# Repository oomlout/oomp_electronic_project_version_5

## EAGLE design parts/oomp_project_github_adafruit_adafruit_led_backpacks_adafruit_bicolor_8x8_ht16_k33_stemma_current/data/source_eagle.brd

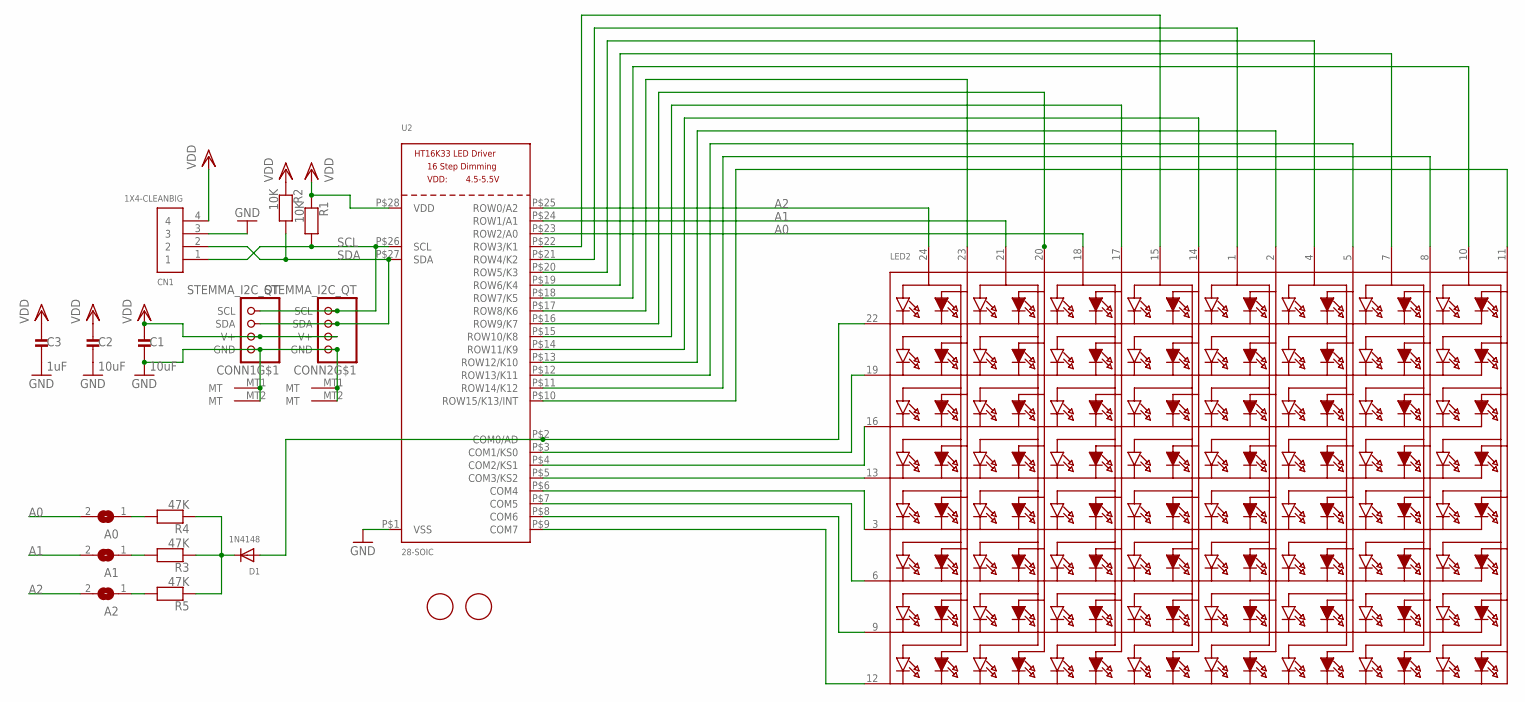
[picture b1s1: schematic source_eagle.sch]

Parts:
A0, A1, A2: SOLDERJUMPERREFLOW_NOPASTE; SOLDERJUMPER_REFLOW_NOPASTE
C1, C2: 10uF; 0805-NO
C3: 1uF; 0603-NO
CN1: 1X4-CLEANBIG; 1X04-CLEANBIG
CONN1, CONN2: STEMMA_I2C_QT; JST_SH4
D1: 1N4148; SOD-323
LED2: DISP_SEGMENT_8X8_BICOLOR_ROWCATHODEMI2A883XX; SEGMENT_BICOL_BL-M12A883XX
R1, R2: 10K; 0603-NO
R3, R4, R5: 47K; 0603-NO
U2: 28-SOIC; SOP28_300MIL
U$1, U$2: FIDUCIAL; FIDUCIAL_1MM

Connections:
A0: A0.2, LED2.18 (A5), U2.P$23 (ROW2/A0)
A1: A1.2, LED2.21 (A3), U2.P$24 (ROW1/A1)
A2: A2.2, LED2.24 (A1), U2.P$25 (ROW0/A2)
GND: C1.2, C2.2, C3.2, CN1.3, CONN1.1 (GND), CONN1.MT1 (MT), CONN1.MT2 (MT), CONN2.1 (GND), CONN2.MT1 (MT), CONN2.MT2 (MT), U2.P$1 (VSS)
unnamed: LED2.12 (K8), U2.P$9 (COM7)
unnamed: LED2.9 (K7), U2.P$8 (COM6)
unnamed: LED2.6 (K6), U2.P$7 (COM5)
unnamed: LED2.3 (K5), U2.P$6 (COM4)
unnamed: LED2.13 (K4), U2.P$5 (COM3/KS2)
unnamed: LED2.16 (K3), U2.P$4 (COM2/KS1)
unnamed: LED2.19 (K2), U2.P$3 (COM1/KS0)
unnamed: D1.A, LED2.22 (K1), U2.P$2 (COM0/AD)
unnamed: A2.1, R5.2
unnamed: LED2.8 (A14), U2.P$11 (ROW14/K12)
unnamed: LED2.5 (A12), U2.P$12 (ROW13/K11)
unnamed: LED2.11 (A16), U2.P$10 (ROW15/K13/INT)
unnamed: D1.C, R3.1, R4.1, R5.1
unnamed: A1.1, R3.2
unnamed: A0.1, R4.2
unnamed: LED2.10 (A15), U2.P$18 (ROW7/K5)
unnamed: LED2.7 (A13), U2.P$19 (ROW6/K4)
unnamed: LED2.1 (A9), U2.P$21 (ROW4/K2)
unnamed: LED2.15 (A7), U2.P$22 (ROW3/K1)
unnamed: LED2.4 (A11), U2.P$20 (ROW5/K3)
unnamed: LED2.23 (A2), U2.P$17 (ROW8/K6)
unnamed: LED2.20 (A4), U2.P$16 (ROW9/K7)
unnamed: LED2.14 (A8), U2.P$14 (ROW11/K9)
unnamed: LED2.17 (A6), U2.P$15 (ROW10/K8)
unnamed: LED2.2 (A10), U2.P$13 (ROW12/K10)
SCL: CN1.1, CONN1.4 (SCL), CONN2.4 (SCL), R1.2, U2.P$26 (SCL)
SDA: CN1.2, CONN1.3 (SDA), CONN2.3 (SDA), R2.2, U2.P$27 (SDA)
VDD: C1.1, C2.1, C3.1, CN1.4, CONN1.2 (V+), CONN2.2 (V+), R1.1, R2.1, U2.P$28 (VDD)

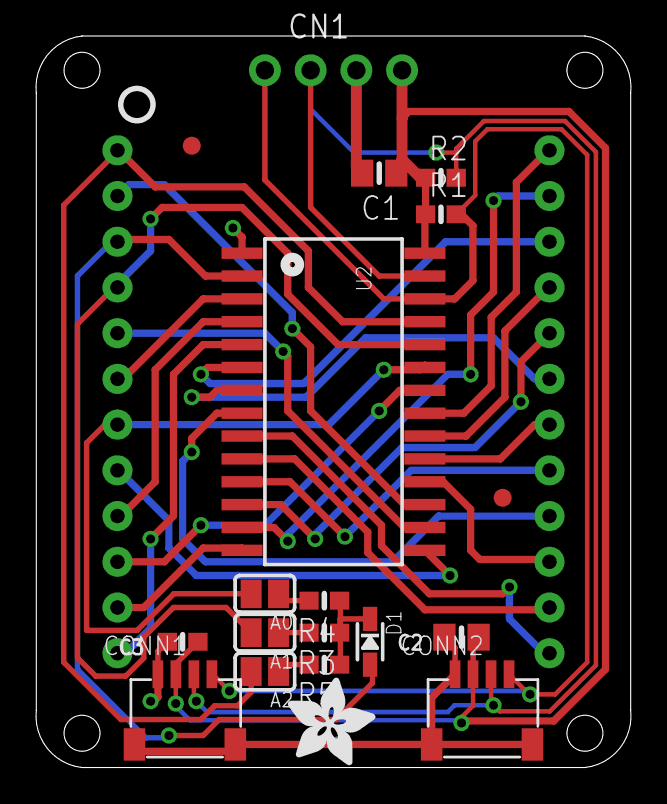
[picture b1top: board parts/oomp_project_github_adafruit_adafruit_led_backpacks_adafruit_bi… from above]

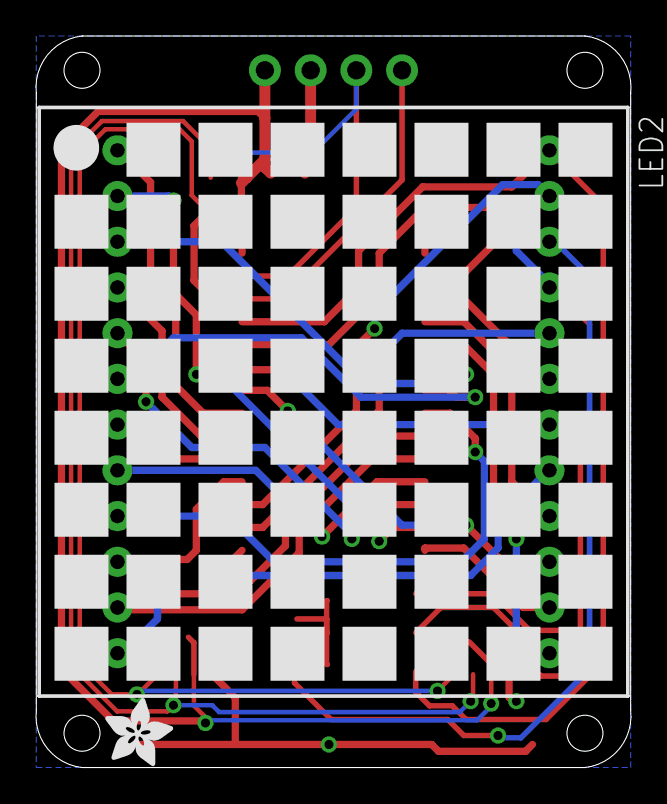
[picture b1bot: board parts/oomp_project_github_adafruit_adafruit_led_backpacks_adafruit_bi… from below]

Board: 2 copper layers, 33.1 x 40.6 mm, 37 parts (7 on the bottom side), 32 nets.

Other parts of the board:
E$2: ADAFRUIT_3.5MM
PLABEL0: PLABEL0
PLABEL1: PLABEL1
PLABEL2: PLABEL2
PLABEL3: PLABEL3
PLABEL4: PLABEL4
PLABEL5: PLABEL5
PLABEL6: PLABEL6
PLABEL7: PLABEL7
PLABEL8: PLABEL8
PLABEL9: PLABEL9
PLABEL10: PLABEL10
PLABEL11: PLABEL11
PLABEL12: PLABEL12
PLABEL13: PLABEL13
PLABEL14: PLABEL14
U$3: ADAFRUIT_5MM
U$4: PCBFEAT-REV-040

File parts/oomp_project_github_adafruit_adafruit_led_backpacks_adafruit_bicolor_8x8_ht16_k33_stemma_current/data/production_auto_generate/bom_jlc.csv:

Comment,Designator,Footprint,LCSC Part #
,E$2,Adafruit Bicolor 8x8 HT16K33 STEMMA-import-fps:ADAFRUIT_3.5MM,
,U$3,Adafruit Bicolor 8x8 HT16K33 STEMMA-import-fps:ADAFRUIT_5MM,
,U$4,Adafruit Bicolor 8x8 HT16K33 STEMMA-import-fps:PCBFEAT-REV-040,
,PLABEL0,Adafruit Bicolor 8x8 HT16K33 STEMMA-import-fps:PLABEL0,
,PLABEL1,Adafruit Bicolor 8x8 HT16K33 STEMMA-import-fps:PLABEL1,
,PLABEL10,Adafruit Bicolor 8x8 HT16K33 STEMMA-import-fps:PLABEL10,
,PLABEL11,Adafruit Bicolor 8x8 HT16K33 STEMMA-import-fps:PLABEL11,
,PLABEL12,Adafruit Bicolor 8x8 HT16K33 STEMMA-import-fps:PLABEL12,
,PLABEL13,Adafruit Bicolor 8x8 HT16K33 STEMMA-import-fps:PLABEL13,
,PLABEL14,Adafruit Bicolor 8x8 HT16K33 STEMMA-import-fps:PLABEL14,
,PLABEL2,Adafruit Bicolor 8x8 HT16K33 STEMMA-import-fps:PLABEL2,
,PLABEL3,Adafruit Bicolor 8x8 HT16K33 STEMMA-import-fps:PLABEL3,
,PLABEL4,Adafruit Bicolor 8x8 HT16K33 STEMMA-import-fps:PLABEL4,
,PLABEL5,Adafruit Bicolor 8x8 HT16K33 STEMMA-import-fps:PLABEL5,
,PLABEL6,Adafruit Bicolor 8x8 HT16K33 STEMMA-import-fps:PLABEL6,
,PLABEL7,Adafruit Bicolor 8x8 HT16K33 STEMMA-import-fps:PLABEL7,
,PLABEL8,Adafruit Bicolor 8x8 HT16K33 STEMMA-import-fps:PLABEL8,
,PLABEL9,Adafruit Bicolor 8x8 HT16K33 STEMMA-import-fps:PLABEL9,
,LED2,Adafruit Bicolor 8x8 HT16K33 STEMMA-import-fps:SEGMENT_BICOL_BL-M12A883XX,
,"A0,A1,A2",Adafruit Bicolor 8x8 HT16K33 STEMMA-import-fps:SOLDERJUMPER_REFLOW_NOPASTE,
10K,"R1,R2",Adafruit Bicolor 8x8 HT16K33 STEMMA-import-fps:0603-NO,C98220
10uF,"C1,C2",Adafruit Bicolor 8x8 HT16K33 STEMMA-import-fps:0805-NO,
1N4148,D1,Adafruit Bicolor 8x8 HT16K33 STEMMA-import-fps:SOD-323,
1uF,C3,Adafruit Bicolor 8x8 HT16K33 STEMMA-import-fps:0603-NO,C5673
1X4-CLEANBIG,CN1,Adafruit Bicolor 8x8 HT16K33 STEMMA-import-fps:1X04-CLEANBIG,
28-SOIC,U2,Adafruit Bicolor 8x8 HT16K33 STEMMA-import-fps:SOP28_300MIL,
47K,"R3,R4,R5",Adafruit Bicolor 8x8 HT16K33 STEMMA-import-fps:0603-NO,C2907042
FIDUCIAL,"U$1,U$2",Adafruit Bicolor 8x8 HT16K33 STEMMA-import-fps:FIDUCIAL_1MM,
STEMMA_I2C_QT,"CONN1,CONN2",Adafruit Bicolor 8x8 HT16K33 STEMMA-import-fps:JST_SH4,C160404

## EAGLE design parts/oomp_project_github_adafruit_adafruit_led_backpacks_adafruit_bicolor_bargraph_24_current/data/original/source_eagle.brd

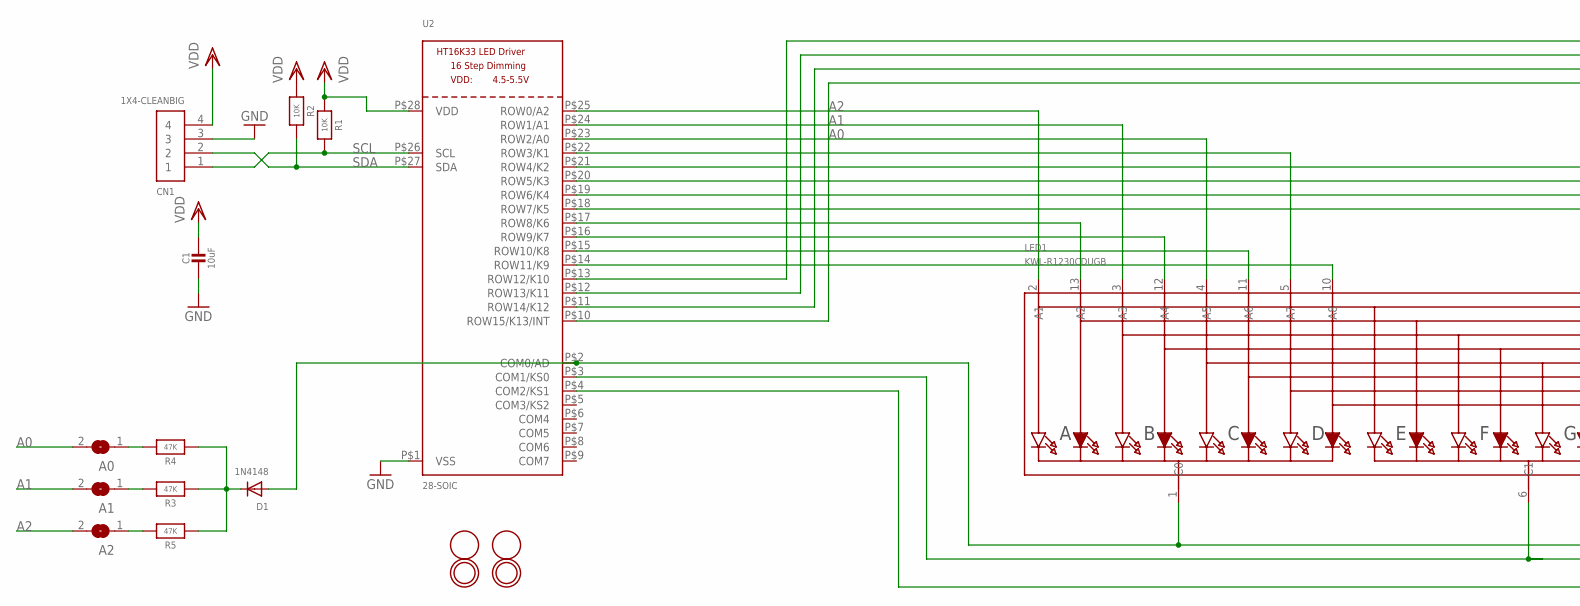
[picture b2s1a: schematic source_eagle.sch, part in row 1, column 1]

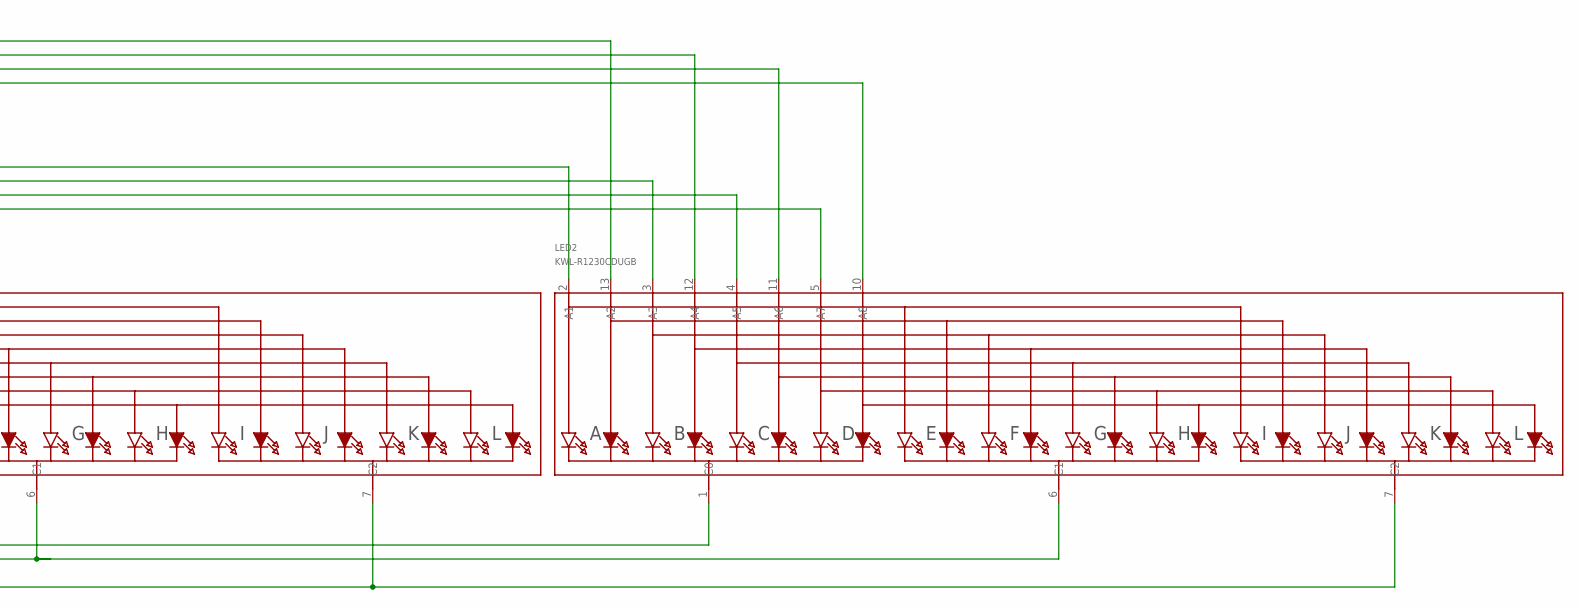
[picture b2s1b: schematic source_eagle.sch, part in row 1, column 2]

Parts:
A0, A1, A2: SOLDERJUMPERREFLOW_NOPASTE; SOLDERJUMPER_REFLOW_NOPASTE
C1: 10uF; 0805-NO
CN1: 1X4-CLEANBIG; 1X04-CLEANBIG
D1: 1N4148; SOD-323F
LED1, LED2: KWL-R1230CDUGB; SEGMENT_BICOL_BL-AR12Z3010
R1, R2: 10K; 0805-NO
R3, R4, R5: 47K; 0805-NO
U2: 28-SOIC; SOP28_300MIL
U$1, U$2: FIDUCIAL; FIDUCIAL_1MM
U$3, U$4: MOUNTINGHOLE2.5; MOUNTINGHOLE_2.5_PLATED

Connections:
A0: A0.2, LED1.4 (A5), U2.P$23 (ROW2/A0)
A1: A1.2, LED1.3 (A3), U2.P$24 (ROW1/A1)
A2: A2.2, LED1.2 (A1), U2.P$25 (ROW0/A2)
C0: D1.A, LED1.1 (C0), LED2.1 (C0), U2.P$2 (COM0/AD)
C1: LED1.6 (C1), LED2.6 (C1), U2.P$3 (COM1/KS0)
C2: LED1.7 (C2), LED2.7 (C2), U2.P$4 (COM2/KS1)
GND: C1.2, CN1.3, U2.P$1 (VSS)
unnamed: LED2.5 (A7), U2.P$18 (ROW7/K5)
unnamed: LED1.13 (A2), U2.P$17 (ROW8/K6)
unnamed: LED2.4 (A5), U2.P$19 (ROW6/K4)
unnamed: A2.1, R5.2
unnamed: D1.C, R3.1, R4.1, R5.1
unnamed: A1.1, R3.2
unnamed: A0.1, R4.2
unnamed: LED2.2 (A1), U2.P$21 (ROW4/K2)
unnamed: LED1.5 (A7), U2.P$22 (ROW3/K1)
unnamed: LED2.3 (A3), U2.P$20 (ROW5/K3)
unnamed: LED1.12 (A4), U2.P$16 (ROW9/K7)
R10: LED1.11 (A6), U2.P$15 (ROW10/K8)
R11: LED1.10 (A8), U2.P$14 (ROW11/K9)
R12: LED2.13 (A2), U2.P$13 (ROW12/K10)
R13: LED2.12 (A4), U2.P$12 (ROW13/K11)
R14: LED2.11 (A6), U2.P$11 (ROW14/K12)
R15: LED2.10 (A8), U2.P$10 (ROW15/K13/INT)
SCL: CN1.1, R1.2, U2.P$26 (SCL)
SDA: CN1.2, R2.2, U2.P$27 (SDA)
VDD: C1.1, CN1.4, R1.1, R2.1, U2.P$28 (VDD)

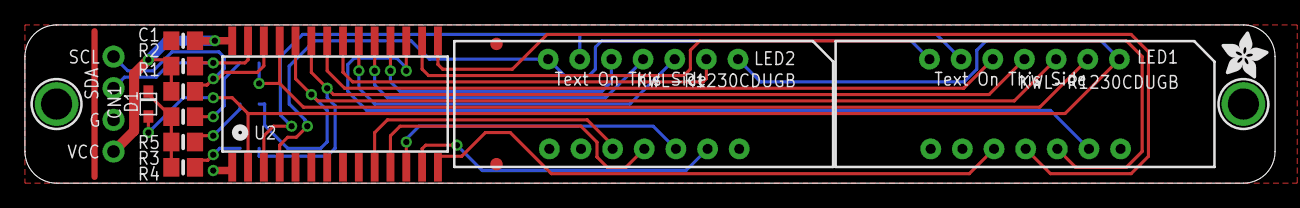
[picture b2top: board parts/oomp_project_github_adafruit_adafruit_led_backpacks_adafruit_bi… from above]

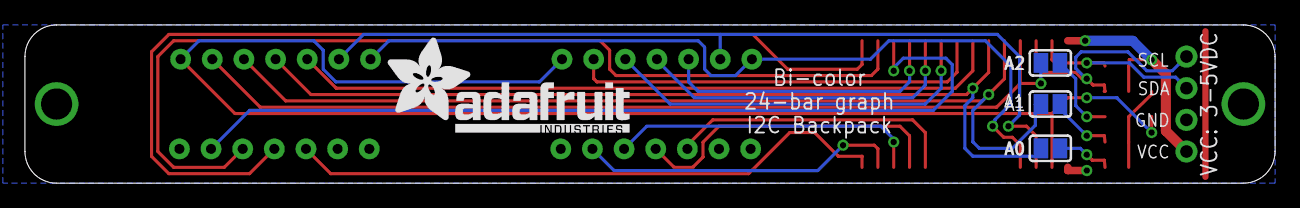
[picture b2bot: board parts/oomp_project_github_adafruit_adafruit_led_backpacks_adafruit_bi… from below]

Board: 2 copper layers, 100.3 x 12.7 mm, 20 parts (4 on the bottom side), 27 nets.

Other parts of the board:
U$5: ADAFRUIT_TEXT_20MM
U$6: ADAFRUIT_3.5MM

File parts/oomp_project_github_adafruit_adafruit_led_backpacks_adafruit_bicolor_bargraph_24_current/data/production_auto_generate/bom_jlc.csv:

Comment,Designator,Footprint,LCSC Part #
,U$6,Adafruit bicolor bargraph 24-import-fps:ADAFRUIT_3.5MM,
,U$5,Adafruit bicolor bargraph 24-import-fps:ADAFRUIT_TEXT_20MM,
,"A0,A1,A2",Adafruit bicolor bargraph 24-import-fps:SOLDERJUMPER_REFLOW_NOPASTE,
10K,"R1,R2",Adafruit bicolor bargraph 24-import-fps:0805-NO,C17414
10uF,C1,Adafruit bicolor bargraph 24-import-fps:0805-NO,
1N4148,D1,Adafruit bicolor bargraph 24-import-fps:SOD-323F,
1X4-CLEANBIG,CN1,Adafruit bicolor bargraph 24-import-fps:1X04-CLEANBIG,
28-SOIC,U2,Adafruit bicolor bargraph 24-import-fps:SOP28_300MIL,
47K,"R3,R4,R5",Adafruit bicolor bargraph 24-import-fps:0805-NO,C17713
FIDUCIAL,"U$1,U$2",Adafruit bicolor bargraph 24-import-fps:FIDUCIAL_1MM,
KWL-R1230CDUGB,"LED1,LED2",Adafruit bicolor bargraph 24-import-fps:SEGMENT_BICOL_BL-AR12Z3010,

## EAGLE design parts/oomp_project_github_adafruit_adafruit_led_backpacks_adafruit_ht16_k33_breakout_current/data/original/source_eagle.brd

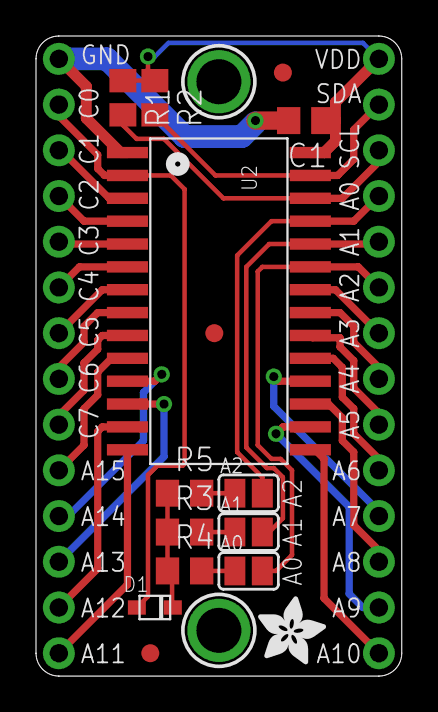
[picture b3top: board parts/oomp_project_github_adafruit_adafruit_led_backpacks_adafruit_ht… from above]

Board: 2 copper layers, 20.3 x 35.6 mm, 20 parts (1 on the bottom side), 32 nets.

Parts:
A0, A1, A2: SOLDERJUMPER_REFLOW_NOPASTE
C1: 10uF; C0805
D1: 1N4148; SOD-323F
JP1, JP2: 1X14-CB
R1, R2: 10K; R0805
R3, R4, R5: 47K; R0805
U2: 28-SOIC; SOP28_300MIL
U$1, U$2, U$6: FIDUCIAL; FIDUCIAL_1MM
U$3: ADAFRUIT_3.5MM
U$4, U$5: MOUNTINGHOLE2.5; MOUNTINGHOLE_2.5_PLATED
U$7: ADAFRUIT_5MM

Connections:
A0: A0.2, JP1.9, U2.P$23
A1: A1.2, JP1.10, U2.P$24
A2: A2.2, JP1.11, U2.P$25
ANOD3: JP1.8, U2.P$22
ANOD4: JP1.7, U2.P$21
ANOD5: JP1.6, U2.P$20
ANOD6: JP1.5, U2.P$19
ANOD7: JP1.4, U2.P$18
ANOD8: JP1.3, U2.P$17
ANOD9: JP1.2, U2.P$16
ANOD10: JP1.1, U2.P$15
ANOD11: JP2.14, U2.P$14
ANOD12: JP2.13, U2.P$13
ANOD13: JP2.12, U2.P$12
ANOD14: JP2.11, U2.P$11
ANOD15: JP2.10, U2.P$10
CATH0: D1.A, JP2.2, U2.P$2
CATH1: JP2.3, U2.P$3
CATH2: JP2.4, U2.P$4
CATH3: JP2.5, U2.P$5
CATH4: JP2.6, U2.P$6
CATH5: JP2.7, U2.P$7
CATH6: JP2.8, U2.P$8
CATH7: JP2.9, U2.P$9
GND: C1.2, JP2.1, U2.P$1
unnamed: A2.1, R5.2
unnamed: D1.C, R3.1, R4.1, R5.1
unnamed: A1.1, R3.2
unnamed: A0.1, R4.2
SCL: JP1.12, R1.2, U2.P$26
SDA: JP1.13, R2.2, U2.P$27
VDD: C1.1, JP1.14, R1.1, R2.1, U2.P$28

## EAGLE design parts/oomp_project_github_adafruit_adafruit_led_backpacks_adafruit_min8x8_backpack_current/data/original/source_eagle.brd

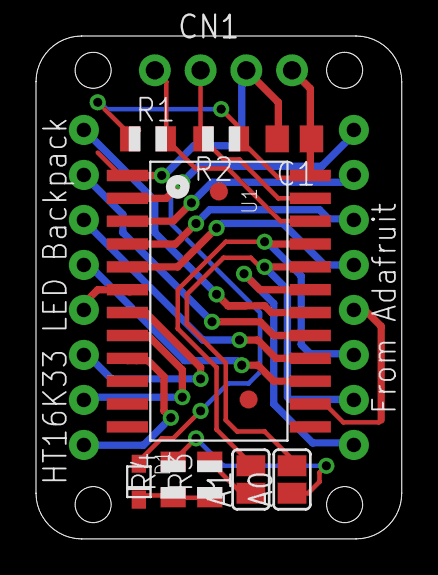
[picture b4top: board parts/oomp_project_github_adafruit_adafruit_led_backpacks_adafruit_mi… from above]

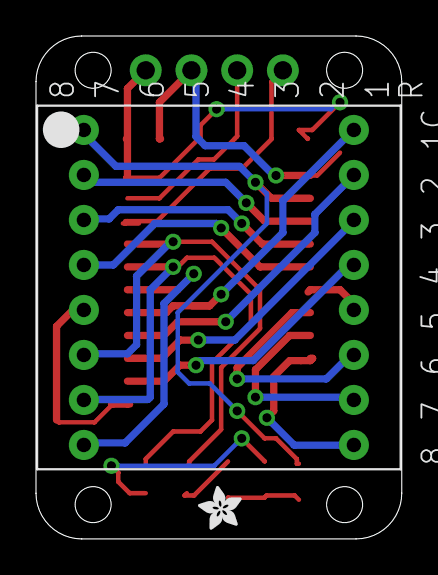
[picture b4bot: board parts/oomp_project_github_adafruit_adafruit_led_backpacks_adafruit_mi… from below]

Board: 2 copper layers, 20.3 x 27.9 mm, 14 parts (2 on the bottom side), 23 nets.

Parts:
A0, A1: SOLDERJUMPER_REFLOW_NOPASTE
C1: 10uF; C0805
CN1: 1X4-CLEANBIG; 1X04-CLEANBIG
D1: 1N4148; SOD-323F
LED1: BL-M07C881UR; SEGMENT_BL-M07C881UR
R1, R2, R3, R4: 10K; R0805
U1: SOP24_300MIL
U$1, U$2: FIDUCIAL; FIDUCIAL_1MM
U$4: ADAFRUIT_2.5MM

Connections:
A0: A0.2, LED1.7, U1.P$20
A1: A1.2, LED1.6, U1.P$21
GND: C1.2, CN1.3, U1.P$1
unnamed: LED1.9, U1.P$9
unnamed: LED1.10, U1.P$8
unnamed: LED1.11, U1.P$7
unnamed: LED1.12, U1.P$6
unnamed: LED1.4, U1.P$5
unnamed: LED1.3, U1.P$4
unnamed: LED1.2, U1.P$3
unnamed: D1.A, LED1.1, U1.P$2
unnamed: LED1.8, U1.P$19
unnamed: LED1.16, U1.P$18
unnamed: LED1.15, U1.P$17
unnamed: D1.C, R3.1, R4.1
unnamed: LED1.5, U1.P$14
unnamed: A1.1, R3.2
unnamed: A0.1, R4.2
SCL: CN1.1, R1.2, U1.P$22
SDA: CN1.2, R2.2, U1.P$23
SEG_F: LED1.14, U1.P$16
SEG_G: LED1.13, U1.P$15
VDD: C1.1, CN1.4, R1.1, R2.1, U1.P$24

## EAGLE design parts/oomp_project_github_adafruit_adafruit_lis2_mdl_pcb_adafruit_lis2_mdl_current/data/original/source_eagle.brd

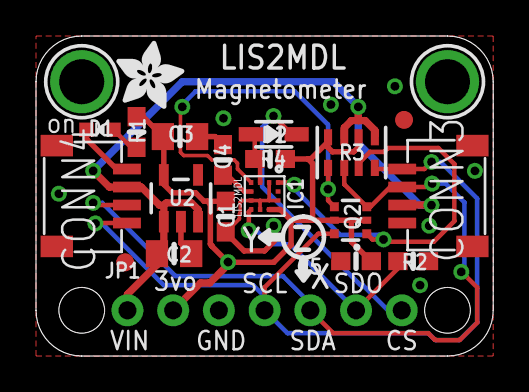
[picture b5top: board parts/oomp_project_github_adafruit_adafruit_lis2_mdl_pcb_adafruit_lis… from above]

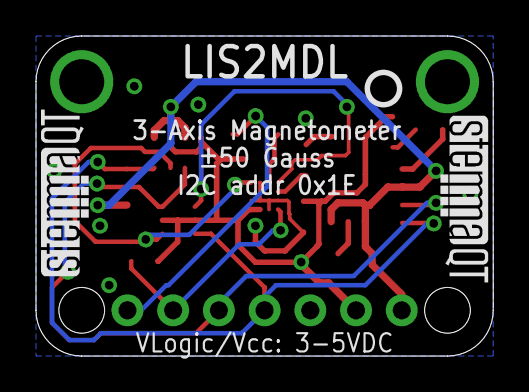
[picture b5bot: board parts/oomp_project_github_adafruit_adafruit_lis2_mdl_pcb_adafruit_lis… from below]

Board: 2 copper layers, 25.4 x 17.8 mm, 25 parts (3 on the bottom side), 12 nets.

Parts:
C1, C4: 0.1uF; 0603-NO
C2, C3: 10uF; 0805-NO
C5: 1uF; 0603-NO
CONN3, CONN4: STEMMA_I2C_QT; JST_SH4
D1: GREEN; CHIPLED_0603_NOOUTLINE
D2: 1N4148; SOD-323
FID3, FID4: FIDUCIAL_1MM
IC1: LIS2MDL; LGA12_2X2MM
JP1: 1X07_ROUND_70
Q2: BSS138; SOT363
R1, R2, R4: 10K; 0603-NO
R3: 10K; RESPACK_4X0603
U2: AP2112K-3.3; SOT23-5
U$1, U$17: MOUNTINGHOLE2.5; MOUNTINGHOLE_2.5_PLATED
U$11: ADAFRUIT_3.5MM
U$25: PCBFEAT-REV-040
U$30, U$31: STEMMAQT

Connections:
3.3V: C1.1, C3.1, C5.1, IC1.9, IC1.10, JP1.2, Q2.2, Q2.5, R1.1, R3.2, R3.4, R4.2, U2.5
CAP: C4.1, IC1.5
CS: D2.C, JP1.7
CS_3V: D2.A, IC1.3, R4.1
GND: C1.2, C2.2, C3.2, C4.2, C5.2, CONN3.1, CONN3.MT1, CONN3.MT2, CONN4.1, CONN4.MT1, CONN4.MT2, D1.C, IC1.2, IC1.6, IC1.8, IC1.11, IC1.12, JP1.3, R2.1, U2.2
unnamed: D1.A, R1.2
SCL: CONN3.4, CONN4.4, JP1.4, Q2.6, R3.8
SCL_3V: IC1.1, Q2.1, R3.7
SDA: CONN3.3, CONN4.3, JP1.5, Q2.3, R3.6
SDA_3V: IC1.4, Q2.4, R3.5
SDO: IC1.7, JP1.6, R2.2
VCC: C2.1, CONN3.2, CONN4.2, JP1.1, R3.1, R3.3, U2.1, U2.3

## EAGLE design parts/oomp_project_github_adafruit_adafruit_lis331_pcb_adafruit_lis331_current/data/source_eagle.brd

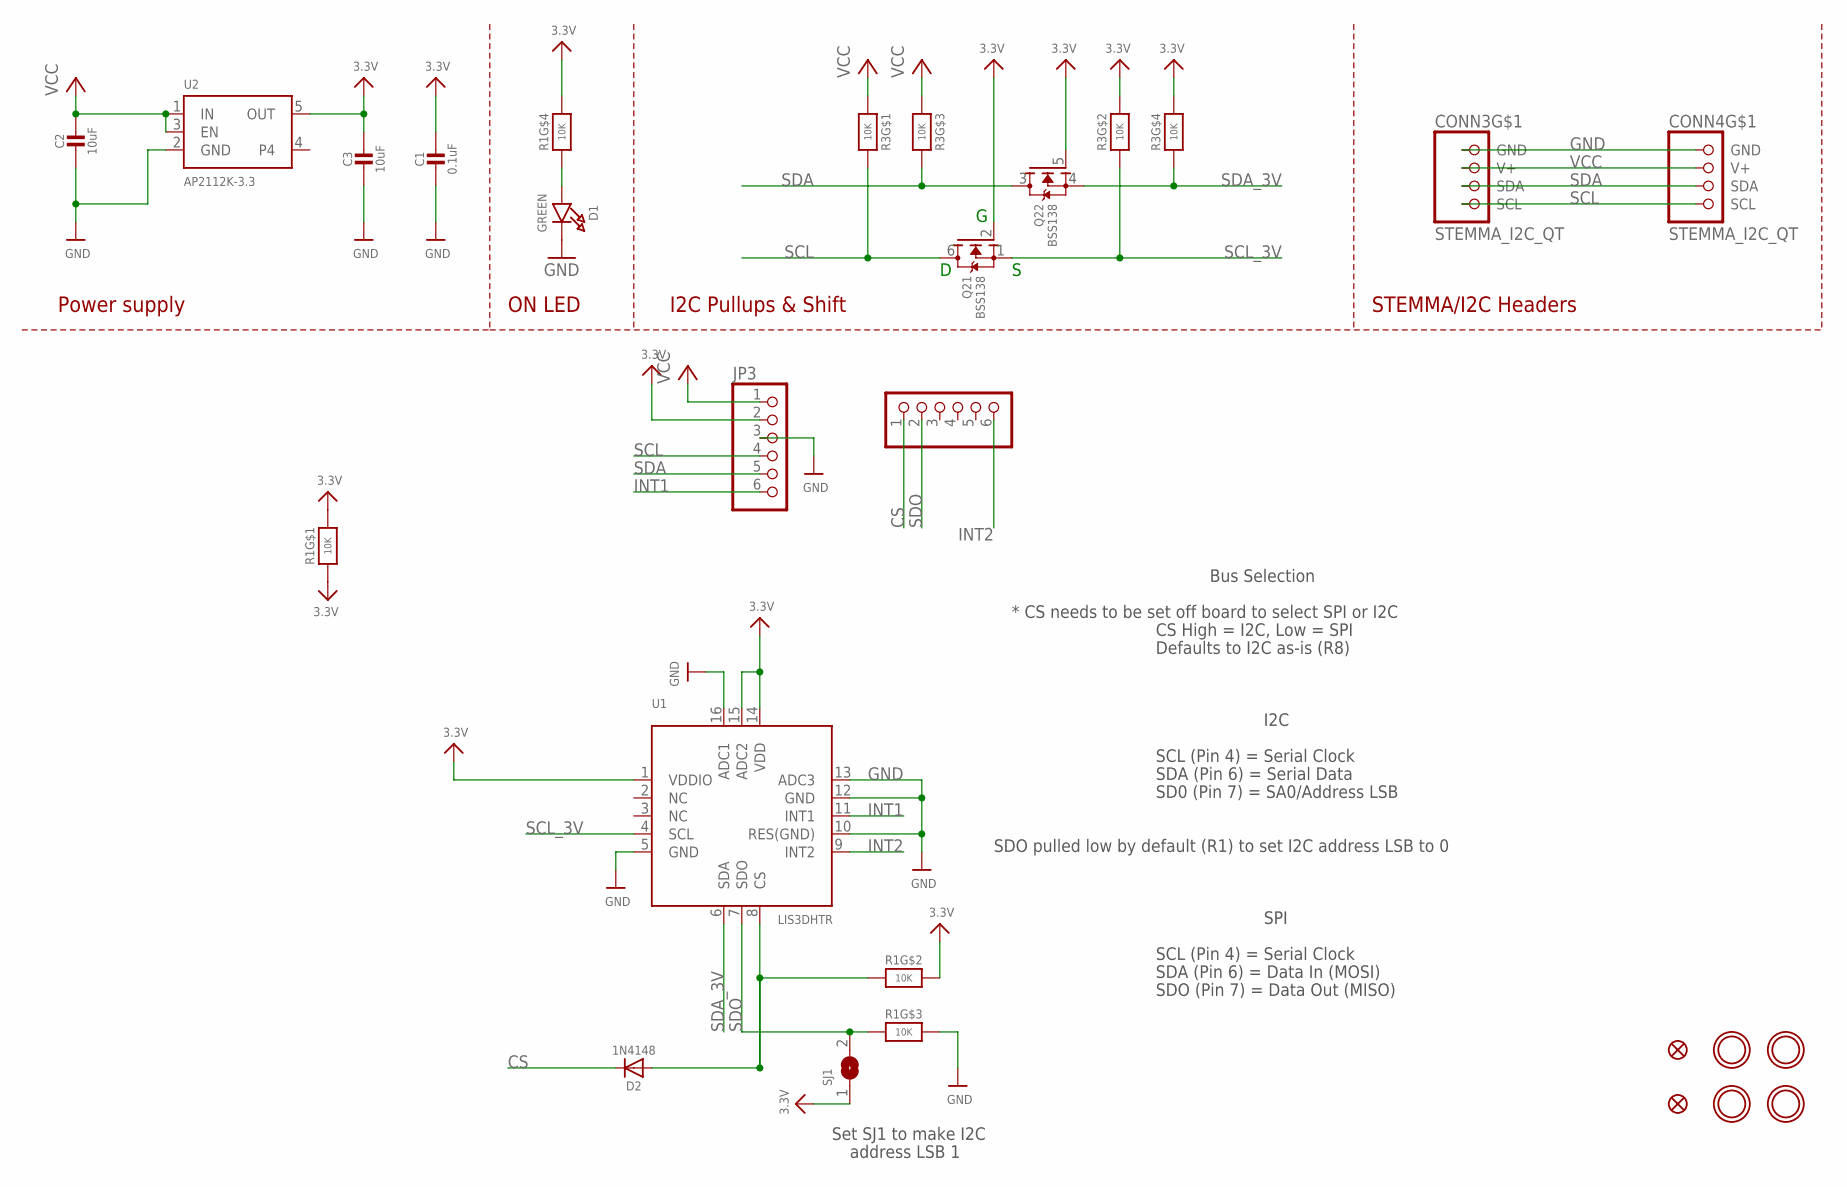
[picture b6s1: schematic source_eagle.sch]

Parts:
C1: 0.1uF; 0603-NO
C2, C3: 10uF; 0805-NO
CONN3, CONN4: STEMMA_I2C_QT; JST_SH4
D1: GREEN; CHIPLED_0603_NOOUTLINE
D2: 1N4148; SOD-323
FID3, FID4: FIDUCIAL_1MM
JP2, JP3: HEADER-1X670MIL; 1X06_ROUND_70
Q2: BSS138; SOT363
R1, R3: 10K; RESPACK_4X0603
SJ1: SOLDERJUMPER; SOLDERJUMPER_ARROW_NOPASTE
U1: LIS3DHTR; LGA16_3X3MM
U2: AP2112K-3.3; SOT23-5
U$1, U$17, U$19, U$21: MOUNTINGHOLE2.5; MOUNTINGHOLE_2.5_PLATED

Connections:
3.3V: C1.1, C3.1, JP3.2, Q2.2 (G), Q2.5 (G), R1.1, R1.5 (2), R1.7 (2), R1.8 (2), R3.2 (1), R3.4 (1), SJ1.1, U1.1 (VDDIO), U1.14 (VDD), U1.15 (ADC2), U2.5 (OUT)
CS: D2.C, JP2.1
GND: C1.2, C2.2, C3.2, CONN3.1 (GND), CONN4.1 (GND), D1.C, JP3.3, R1.6 (2), U1.5 (GND), U1.10 (RES(GND)), U1.12 (GND), U1.13 (ADC3), U1.16 (ADC1), U2.2 (GND)
INT1: JP3.6, U1.11 (INT1)
INT2: JP2.6, U1.9 (INT2)
unnamed: D1.A, R1.4 (1)
unnamed: D2.A, R1.2 (1), U1.8 (CS)
SCL: CONN3.4 (SCL), CONN4.4 (SCL), JP3.4, Q2.6 (D), R3.8 (2)
SCL_3V: Q2.1 (S), R3.7 (2), U1.4 (SCL)
SDA: CONN3.3 (SDA), CONN4.3 (SDA), JP3.5, Q2.3 (D), R3.6 (2)
SDA_3V: Q2.4 (S), R3.5 (2), U1.6 (SDA)
SDO: JP2.2, R1.3 (1), SJ1.2, U1.7 (SDO)
VCC: C2.1, CONN3.2 (V+), CONN4.2 (V+), JP3.1, R3.1, R3.3 (1), U2.1 (IN), U2.3 (EN)

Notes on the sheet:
I2C Pullups & Shift
STEMMA/I2C Headers
ON LED
Power supply
I2C
SCL (Pin 4) = Serial Clock
SDA (Pin 6) = Serial Data
SD0 (Pin 7) = SA0/Address LSB
* CS needs to be set off board to select SPI or I2C
CS High = I2C, Low = SPI
Defaults to I2C as-is (R8)
SDO pulled low by default (R1) to set I2C address LSB to 0
Bus Selection
SPI
SDA (Pin 6) = Data In (MOSI)
SDO (Pin 7) = Data Out (MISO)
Set SJ1 to make I2C
address LSB 1

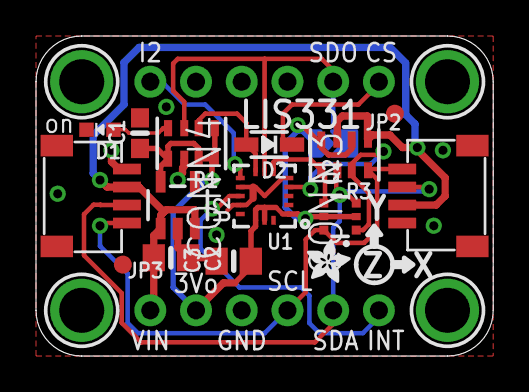
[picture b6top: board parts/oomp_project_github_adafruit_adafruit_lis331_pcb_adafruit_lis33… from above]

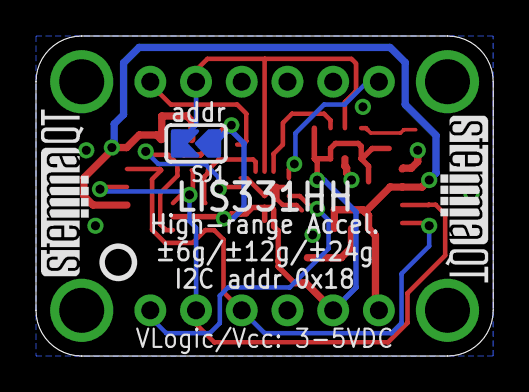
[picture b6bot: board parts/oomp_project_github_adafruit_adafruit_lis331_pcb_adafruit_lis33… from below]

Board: 2 copper layers, 25.4 x 17.8 mm, 25 parts (4 on the bottom side), 13 nets.

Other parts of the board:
U$12: ADAFRUIT_2.5MM
U$25: PCBFEAT-REV-040
U$30, U$31: STEMMAQT

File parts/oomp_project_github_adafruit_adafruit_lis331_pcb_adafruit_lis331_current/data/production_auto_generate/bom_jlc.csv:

Comment,Designator,Footprint,LCSC Part #
,"JP2,JP3",Adafruit_LIS331-import-fps:1X06_ROUND_70,C37208
,U$12,Adafruit_LIS331-import-fps:ADAFRUIT_2.5MM,
,U$25,Adafruit_LIS331-import-fps:PCBFEAT-REV-040,
,"U$30,U$31",Adafruit_LIS331-import-fps:STEMMAQT,
0.1uF,C1,Adafruit_LIS331-import-fps:0603-NO,C14663
10K,"R1,R3",Adafruit_LIS331-import-fps:RESPACK_4X0603,C98220
10uF,"C2,C3",Adafruit_LIS331-import-fps:0805-NO,
1N4148,D2,Adafruit_LIS331-import-fps:SOD-323,
AP2112K-3.3,U2,Adafruit_LIS331-import-fps:SOT23-5,
BSS138,Q2,Adafruit_LIS331-import-fps:SOT363,
GREEN,D1,Adafruit_LIS331-import-fps:CHIPLED_0603_NOOUTLINE,
LIS3DHTR,U1,Adafruit_LIS331-import-fps:LGA16_3X3MM,
STEMMA_I2C_QT,"CONN3,CONN4",Adafruit_LIS331-import-fps:JST_SH4,C160404

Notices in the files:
parts and their libraries:
microbuilder: This work is placed in the public domain, and may be freely used for commercial and non-commercial work with the following conditions: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
